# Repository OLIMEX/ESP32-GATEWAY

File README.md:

# ESP32-GATEWAY
ESP32 WiFi / BLE development board with Ethernet, microSD card, GPIOs, made with KiCAD

Board page: https://www.olimex.com/Products/IoT/ESP32/ESP32-GATEWAY/open-source-hardware

Hardware is released under Apache 2.0 License

Box design is released under CC BY 4.0 License

Software is released under GPL3 License

Documentation is released under CC BY-SA 3.0

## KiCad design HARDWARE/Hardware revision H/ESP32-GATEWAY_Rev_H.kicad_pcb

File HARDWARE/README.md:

# ESP32-GATEWAY
ESP32 WIFI / BLE development board with Ethernet, micro SD card, GPIOs made with KiCAD.

Notice that we use the latest nightly KiCad builds.

Hardware change log:

- Hardware revision I

1. To reduce noise getting picked by Ethernet clock, disconnected GPIO17 from the CON1 header. Added 
jumper pads GPIO17_E1 (open by default) if somebody wants to lead it to the header...

---

- Hardawre revision H

1. Added diode D5 on esp_en;
3. Added TVS1 on PHY;
4. Opravi se value na NA(HN1x20);
5. T1 now LMUN2211LT1G;
6. USB connector changed to type C (more popular nowadays);
7. Added r12 and c6;
8. Added CE sign;
9. R28,R31,R32,R33 lowered to 0402 size;
10. DCDC - SY8089 changed to TPS62A02ADRLR. C3 now NA. L2 changed to 1.0uH/2.5A/CD32;
11. Updated the CH340X module to the latest one. 

---

- Hardware revision G

1. R54 removed. R24 and R16 moved further away from the button.
2. Improved EN signal - added C5(1uF/0603) on pin #3 of ESP32. R24 now 10k.

---

- Hardware revision F

- Added 3D view. Major changes to GPIO header, SD card mode, power consumption!:

1. GPIO6-11, which are used by the ESP32's internal flash, were disconnected from CON1 
and the 6 SD card signals are now routed instead for use when SD card is not present;
2.  SD card changed from 4-bit mode of operation to 1-bit mode of operation! Added 3 
NA resistor pads (R9-R11) for backwards compatiblity.
3. A lot of deep sleep mode improvements to lower the consumption to 100uA or less:

- R19 was changed from 4.99k/1%/R0603 to 220k/R0603;

- R20 was changed from 1.1k/1%/R0603 to 49.9k/1%/R0603;

- R30 was changed from 10k/0603 to 1M/R0603;

- LED_E1 jumper added to provide an option to disable the power LED;

- R24 changed from 1k/0603 to 1M/R0603;

- U5(CH340)'s pin 20disconnected from GND and left opened;

- CH340 now powered only when USB is present;

- R35 and R40 were changed from 220R/R0603 to 10k/R0603;

- D1 and D3 added, 1N5819S4/SOD123, as level shifters;

4. L2 was changed from 2.2uH/1.5A/DCR<0.1R/CD32 to 2.2uH/1.5A/DCR=72mR/20%/3.00x3.00x1.50mm/CD32(NR3015T2R2M);
5. U3's value was changed from ESP-WROOM-32 to ESP32-WROOM-32D-4MB;
6. U9(BAT54C(SOT23-3)) was renamed to D4;

---

- Hardware revision E1

1. Added C2/22uF/0603 for slower PHY powering

- Hardware revision E

1. R5 connected after T1's collector and value changed from NA to 1K. 
2. Improved drill distances.

- Hardware revision D

>Major Ethernet schematic changes, now similar to ESP32-PoE:

1. LAN8710's pin XTAL1 was disconnected from GPIO0 and connected to GPIO17/EMAC_CLK_OUT_180. GPIO17 
is now source clock. GPIO5 is now used as Ethernet "power enable pin".
2. CR1(Q50MHz/25ppm/3V/4P/5x3.2mm) and all surrounding elements were deleted.
3. U8(NCP303LSN27T1G(SOT-23-5)) and all surrounding elements were deleted.
4. U10(BAT54C), R44 and R5 were deleted.
5. FET1, R5, R6, C2, T1 and L1 were added to enable Ethernet power on/off feature.
6. GPIO5 is used for Ethernet power on/off.

- Hardware revision C

1. R5(1k) resistor added between OSC_EN and NRST(pin #19) of LAN8710A chip. Later, it was changed to NA!
2. U2 changed from SY8009AAAC(SOT23-5) to SY8089AAAC(SOT23-5).
3. FET2 changed from IRLML6402 to WPM2015-3/TR.
4. ESP32-WROOM module pad improvements 

>Major changes to the Ethernet PHY and reset similar to EVB's_Rev_D1:

5. U8 changed from BD5230G-TR(SSOP5/SOT-23-5) to NCP303LSN27T1G(SOT-23-5).
6. C28 changed from 10nF/50V/20%/Y5V/C0603 to 470nF/16V/10%/X7R/C0603.
7. C18 changed from 10uF/6.3V/20%/X5R/C0603 to NA.
8. R38 changed from 100k to 10k/R0603.
9. R5 changed from 1k/R0603 to NA.

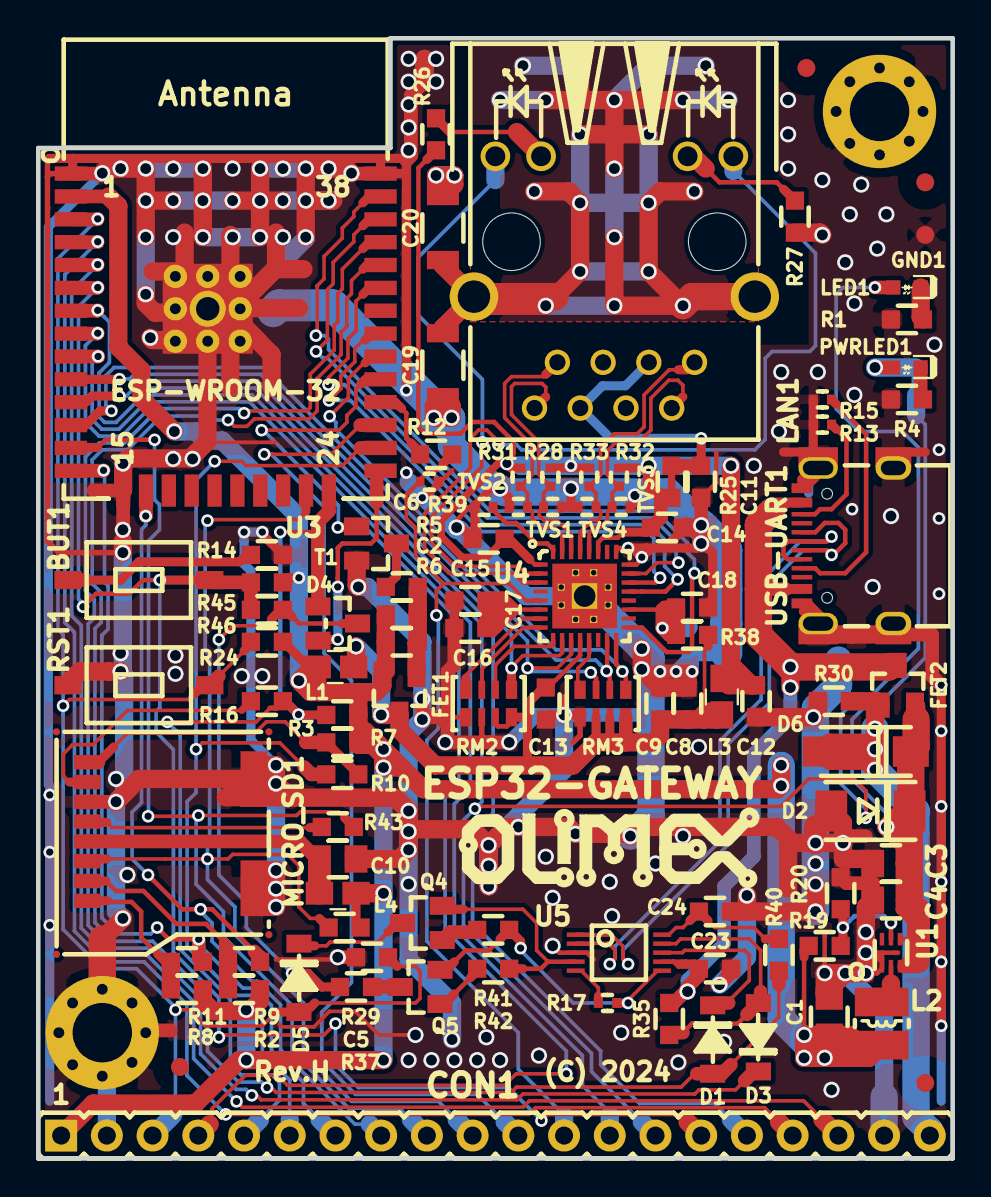
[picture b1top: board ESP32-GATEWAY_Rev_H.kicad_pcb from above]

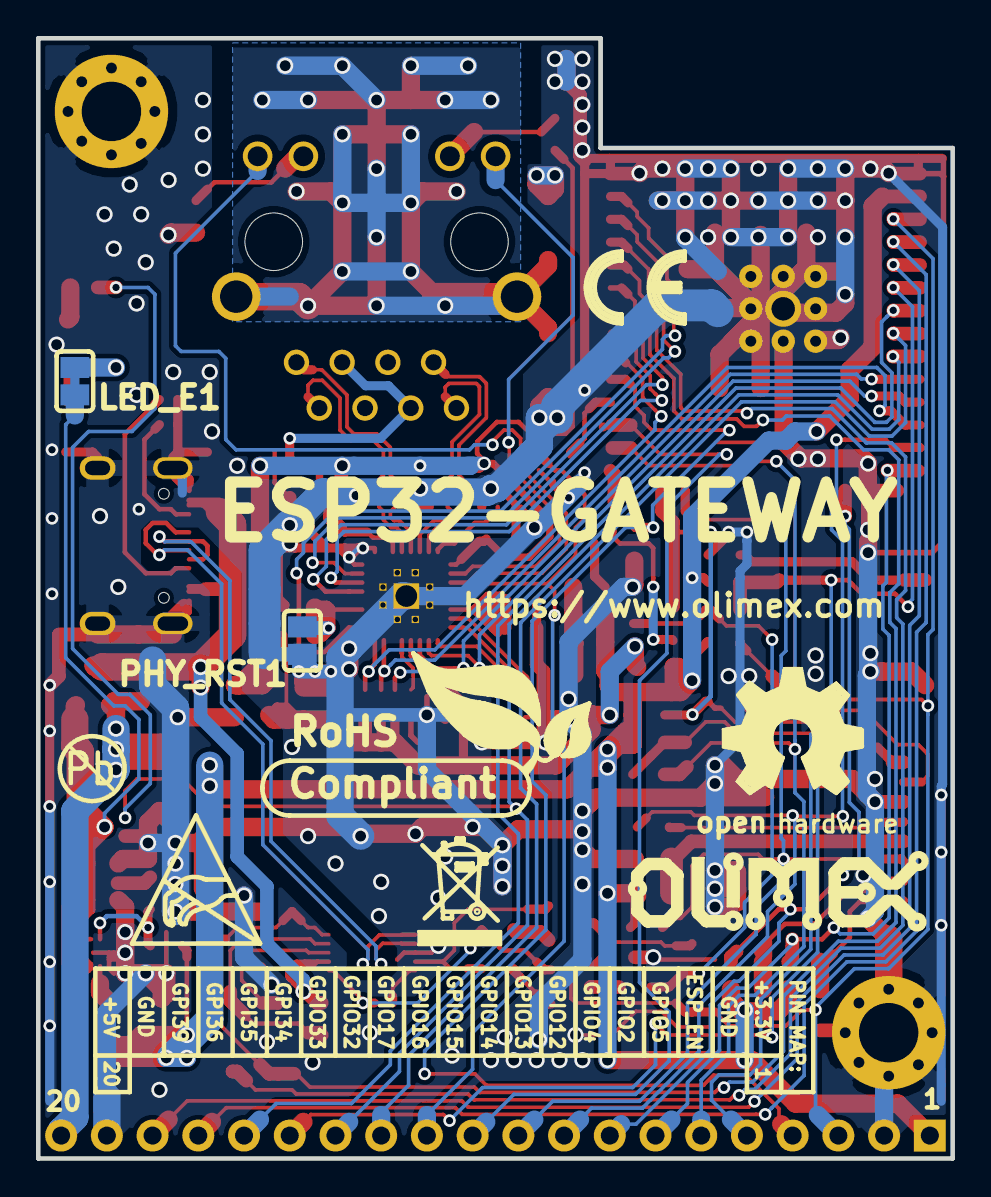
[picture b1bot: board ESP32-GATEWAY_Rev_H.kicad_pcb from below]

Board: 2 copper layers, 50.8 x 62.2 mm, 110 parts (9 on the bottom side), 79 nets.

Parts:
BUT1: T1107A(6x3,8x2,5MM)
C1, C4, C10: 47uF/6.3V/20%/X5R/C0805; C_0805_5MIL_DWS
C2, C8, C9, C12, C23: 22uF/6.3V/20%/X5R/C0603; C_0603_5MIL_DWS
C3: NA(47uF/6.3V/20%/X5R/C0805); C_0805_5MIL_DWS
C5: 1uF/C0603; C_0603_5MIL_DWS
C6: NA/C0402; C_0402_5MIL_DWS
C11, C13, C14, C15, C17, C24: 100nF/50V/20%/Y5V/C0603; C_0603_5MIL_DWS
C16: 2.2uF/6.3V/10%/X5R/C0603; C_0603_5MIL_DWS
C18: NA(10uF/6.3V/20%/X5R/C0603); C_0603_5MIL_DWS
C19: 1nF/2000V/10%/X7R/C1206; C_1206_5MIL_DWS_ISO
C20: NA(1nF/2000V/10%/X7R/C1206); C_1206_5MIL_DWS_ISO
CON1: NA(HN1x20); HN1x20
D1, D3, D5: 1N5819S4/SOD123; SOD-123_1C-2A_KA
D2: SMBJ6.0A(DO-214AA); DO214AA_1(K)-2(A)
D4: BAT54C(SOT23-3); SOT23-3
D6: 1N5822/SS34/SMA; SMA-KA
FET1, FET2: WPM2015-3/TR; SOT23
FID1, FID3: Fiducial; Fiducial1x3
FID2, FID4: Fiducial; Fiducial1x3_Past
GND1: TESTPAD; TESTPAD_40-ROUND
L1: NA(FB0805/600R/2A); L_0805_5MIL_DWS
L2: 1.0uH/2.5A/DCR=30mR/20%/3.00x3.00x1.50mm/CD32(SWP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; CD32
L3, L4: 600OHM/2A/UPZ2012E-601-2R0TF; L_0805_5MIL_DWS
LAN1: RJLD-060TC1(LPJ4013EDNL); RJLBC-060TC1
LED1: LED/GREEN/0603; LED_0603_KA
LED_E1: Closed; SJ
Logo-OLimeX: OLIMEX_LOGO_TB
Logo-OSHW: LOGO_OPENHARDWARE_8x8
Logo-OlimexBIG: OLIMEX_LOGO_TB
MH1, MH2: Mounting_hole_Shield_3.3mm
MICRO_SD1: TFC-WXCP11-08-LF
PHY_RST1: Opened; SJ
PWRLED1: LED/RED/0603; LED_0603_KA
Q4, Q5: BC817-40(SOT23); SOT23
R1, R2, R3, R4, R7, R8: 2.2k/R0603; R_0603_5MIL_DWS
R5, R41, R42: 1k/R0603; R_0603_5MIL_DWS
R6, R24, R29, R35, R38, R40, R45: 10k/R0603; R_0603_5MIL_DWS
R9, R10, R11, R46: NA/R0603; R_0603_5MIL_DWS
R12: 33R/R0603; R_0603_5MIL_DWS
R13, R15: 5.1k/1%/R0402; R_0402_5MIL_DWS
R14, R16, R37: 220R/R0603; R_0603_5MIL_DWS
R17: 4.7k/R0402; R_0402_5MIL_DWS
R19: 220k/R0603; R_0603_5MIL_DWS
R20: 49.9k/1%/R0603; R_0603_5MIL_DWS
R25: 0R(Board_Mounted); R_0603_5MIL_DWS
R26, R27: 330R/R0603; R_0603_5MIL_DWS
R28, R31, R32, R33: 49.9R/1%/R0402; R_0402_5MIL_DWS
R30: 1M/R0603; R_0603_5MIL_DWS
R39: 12.1k/1%/R0402; R_0402_5MIL_DWS
R43: 10R/R0603; R_0603_5MIL_DWS
RM2, RM3: RA1206_(4X0603)_4B8_2.2k; R_MATRIX_4
RST1: T1107A(6x3,8x2,5MM)
Sign-Antistatic: Val**; LOGO_ANTISTATIC_1
Sign-RecyclBin: LOGO_RECYCLEBIN_1
Sign_CE: CE_Sign
Sign_Pb-Free: LOGO_PBFREE
Sign_RoHS: Val**; LOGO_ROHS_1
T1: LMUN2211LT1G; SOT23
TVS1, TVS2, TVS3, TVS4: GG0402052R542P; D_0402_5MIL_DWS
U1: TPS62A02ADRLR(SOT-563-6); SOT-563-6
U3: ESP32-WROOM-32E-N4; ESP-WROOM-32_MODULE
U4: LAN8710A-EZC-ABC; QFN32_EP(33)_5.00x5.00x0.90mm_Pitch_0.50mm
U5: CH340X(MSOP-10); MSOP-10_Pitch-0.5mm_3.00x3.00x1.00mm
USB-UART1: USB-C-16P-F-PTH; USB2.0_TYPE-C(A40-00119-A52-12)

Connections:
+3.3VLAN: C8.1, C9.1, C13.1, FET1.3, L1.2, L3.1, R38.2, RM2.3.1, RM2.4.1, RM3.1.2, RM3.2.2, RM3.3.2, U4.12
+3V3: C1.1, C2.1, CON1.1, FET1.2, L1.1, L2.2, L4.1, R2.1, R3.1, R6.1, R7.1, R8.1, R19.2, R24.1, R29.1, R45.1, U3.2
+5V: C3.1, C4.1, D2.1, D6.1, FET2.2, LED_E1.1, LED_E1.2, PWRLED1.2, U1.3, U1.4
+5V_EXT: CON1.20, D6.2, FET2.1, R30.1
/+5V_USB: C23.1, FET2.3, R35.1, U5.7, USB-UART1.A4, USB-UART1.A9, USB-UART1.B4, USB-UART1.B9
/D+: U5.1, USB-UART1.A6, USB-UART1.B6
/D-: U5.2, USB-UART1.A7, USB-UART1.B7
/D_Com: D4.3, R37.2, R46.2
/ESP_EN: C5.1, CON1.3, D5.2, R24.2, RST1.1, U3.3
/GPI34\BUT1: BUT1.1, CON1.15, R45.2, R46.1, U3.6
/GPI35: CON1.16, U3.7
/GPI36: CON1.17, U3.4
/GPI39: CON1.18, U3.5
/GPIO0: D4.2, U3.25
/GPIO1\U0TXD: D3.1, U3.35
/GPIO2\HS2_DATA0: CON1.5, D4.1, R3.2, R16.1, U3.24
/GPIO3\U0RXD: D1.2, R40.2, U3.34
/GPIO4\HS2_DATA1: CON1.6, R10.1, U3.26
/GPIO5\PHY_PWR: CON1.4, T1.1, U3.29
/GPIO12\HS2_DATA2: CON1.7, R11.1, U3.14
/GPIO13\HS2_DATA3: CON1.8, R9.1, U3.16
/GPIO14\HS2_CLK: CON1.9, R43.1, U3.13
/GPIO15\HS2_CMD: CON1.10, MICRO_SD1.3, R29.2, U3.23
/GPIO16: CON1.11, U3.27
/GPIO17\EMAC_CLK_OUT_180: C6.1, CON1.12, R12.2, U4.5
/GPIO18\MDIO(RMII): RM3.1.1, U3.30, U4.16
/GPIO19\EMAC_TXD0(RMII): U3.31, U4.22
/GPIO21\EMAC_TX_EN(RMII): U3.33, U4.21
/GPIO22\EMAC_TXD1(RMII): U3.36, U4.23
/GPIO23\MDC(RMII): U3.37, U4.17
/GPIO25\EMAC_RXD0(RMII): RM3.3.1, U3.10, U4.11
/GPIO26\EMAC_RXD1(RMII): RM2.4.2, U3.11, U4.10
/GPIO27\EMAC_RX_CRS_DV: RM3.2.1, U3.12, U4.15
/GPIO32: CON1.13, U3.8
/GPIO33\LED: CON1.14, LED1.2, U3.9
/PHYAD0: RM3.4.1, U4.13
/PHYAD1: RM2.1.2, U4.7
/PHYAD2: RM2.2.2, U4.8
/RMIISEL: RM2.3.2, U4.9
/VDD1A-2A: C11.1, C12.1, C14.1, C15.1, L3.2, LAN1.3, LAN1.6, R25.1, R25.2, R26.1, R28.1, R31.1, R32.1, R33.1, U4.1, U4.27
/VDDCR: C16.1, C17.1, U4.6
GND: C1.2, C3.2, C4.2, C5.2, C6.2, C8.2, C9.2, C10.2, C11.2, C12.2, C13.2, C14.2, C15.2, C16.2, C17.2, C18.1, C19.2, C20.2, C23.2, C24.2, CON1.2, CON1.19, D2.2, GND1.1, MH1.GND1, MH2.GND1, MICRO_SD1.6, MICRO_SD1.SH1, MICRO_SD1.SH2, PHY_RST1.1, R1.1, R4.2, R13.2, R14.2, R15.2, R20.2, R27.2, R30.2, R39.2, RM2.1.1, RM2.2.1, RM3.4.2, RST1.2, T1.2, TVS1.1, TVS2.1, TVS3.2, TVS4.2, U1.1, U3.1, U3.15, U3.38, U3.39, U4.24, U4.25, U4.33, U5.3, USB-UART1.0, USB-UART1.A1, USB-UART1.A12, USB-UART1.B1, USB-UART1.B12
unnamed: BUT1.2, R14.1
unnamed: C2.2, FET1.1, R5.1, R6.2
unnamed: C10.1, L4.2, MICRO_SD1.4
unnamed: C18.2, PHY_RST1.2, R38.1, U4.19
unnamed: C19.1, C20.1, LAN1.GND1, LAN1.GND2
unnamed: C24.1, R40.1, U5.10
unnamed: D1.1, U5.8
unnamed: D3.2, R35.2, U5.9
unnamed: D5.1, Q4.3
unnamed: L2.1, U1.2
unnamed: LAN1.1, R33.2, TVS4.1, U4.29
unnamed: LAN1.2, R32.2, TVS3.1, U4.28
unnamed: LAN1.7, R31.2, TVS2.2, U4.31
unnamed: LAN1.8, R28.2, TVS1.2, U4.30
unnamed: LAN1.AG1, R26.2
unnamed: LAN1.AY1, U4.3
unnamed: LAN1.KG1, U4.2
unnamed: LAN1.KY1, R27.1
unnamed: LED1.1, R1.2
unnamed: MICRO_SD1.1, R8.2, R11.2
unnamed: MICRO_SD1.2, R2.2, R9.2
unnamed: MICRO_SD1.5, R43.2
unnamed: MICRO_SD1.7, R16.2
unnamed: MICRO_SD1.8, R7.2, R10.2
unnamed: PWRLED1.1, R4.1
unnamed: Q4.1, R41.2
unnamed: Q4.2, R42.1, U5.4
unnamed: Q5.1, R42.2
unnamed: Q5.2, R17.2, R41.1, U5.6
unnamed: Q5.3, R37.1
unnamed: R5.2, T1.3
unnamed: R12.1, U3.28
unnamed: R13.1, USB-UART1.B5
unnamed: R15.1, USB-UART1.A5
unnamed: R17.1, U5.5
unnamed: R19.1, R20.1, U1.5
unnamed: R39.1, U4.32

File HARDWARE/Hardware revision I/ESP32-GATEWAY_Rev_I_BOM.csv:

"Id";"Designator";"Package";"Quantity";"Designation";"Supplier and ref";
1;"U4";"QFN32_EP(33)_5.00x5.00x0.90mm_Pitch_0.50mm";1;"LAN8710A-EZC-ABC";;;
2;"USB-UART1";"USB2.0_TYPE-C(A40-00119-A52-12)";1;"USB-C-16P-F-PTH";;;
3;"D3,D1,D5";"SOD-123_1C-2A_KA";3;"1N5819S4/SOD123";;;
4;"R19";"R_0603_5MIL_DWS";1;"220k/R0603";;;
5;"R35,R29,R6,R45,R40,R38,R24";"R_0603_5MIL_DWS";7;"10k/R0603";;;
6;"U5";"MSOP-10_Pitch-0.5mm_3.00x3.00x1.00mm";1;"CH340X(MSOP-10)";;;
7;"U3";"ESP-WROOM-32_MODULE";1;"ESP32-WROOM-32E-N4";;;
8;"Sign_CE";"CE_Sign";1;"CE_Sign";;;
9;"LED_E1";"SJ";1;"Closed";;;
10;"MICRO_SD1";"TFC-WXCP11-08-LF";1;"TFC-WXCP11-08-LF";;;
11;"Logo-OlimexBIG,Logo-OLimeX";"OLIMEX_LOGO_TB";2;"";;;
12;"R5,R42,R41";"R_0603_5MIL_DWS";3;"1k/R0603";;;
13;"L1";"L_0805_5MIL_DWS";1;"NA(FB0805/600R/2A)";;;
14;"C2,C23,C12,C9,C8";"C_0603_5MIL_DWS";5;"22uF/6.3V/20%/X5R/C0603";;;
15;"T1";"SOT23";1;"LMUN2211LT1G";;;
16;"FET1,FET2";"SOT23";2;"WPM2015-3/TR";;;
17;"D2";"DO214AA_1(K)-2(A)";1;"SMBJ6.0A(DO-214AA)";;;
18;"R3,R2,R1,R4,R8,R7";"R_0603_5MIL_DWS";6;"2.2k/R0603";;;
19;"Sign_RoHS";"LOGO_ROHS_1";1;"Val**";;;
20;"Sign-RecyclBin";"LOGO_RECYCLEBIN_1";1;"";;;
21;"Sign_Pb-Free";"LOGO_PBFREE";1;"";;;
22;"Logo-OSHW";"LOGO_OPENHARDWARE_8x8";1;"";;;
23;"Sign-Antistatic";"LOGO_ANTISTATIC_1";1;"Val**";;;
24;"LED1";"LED_0603_KA";1;"LED/GREEN/0603";;;
25;"CON1";"HN1x20";1;"NA(HN1x20)";;;
26;"R37,R16,R14";"R_0603_5MIL_DWS";3;"220R/R0603";;;
27;"C4,C10,C1";"C_0805_5MIL_DWS";3;"47uF/6.3V/20%/X5R/C0805";;;
28;"C3";"C_0805_5MIL_DWS";1;"NA(47uF/6.3V/20%/X5R/C0805)";;;
29;"R20";"R_0603_5MIL_DWS";1;"49.9k/1%/R0603";;;
30;"R46,R10,R9,R11";"R_0603_5MIL_DWS";4;"NA/R0603";;;
31;"R30";"R_0603_5MIL_DWS";1;"1M/R0603";;;
32;"D6";"SMA-KA";1;"1N5822/SS34/SMA";;;
33;"C24,C17,C15,C14,C13,C11";"C_0603_5MIL_DWS";6;"100nF/50V/20%/Y5V/C0603";;;
34;"C20";"C_1206_5MIL_DWS_ISO";1;"NA(1nF/2000V/10%/X7R/C1206)";;;
35;"C19";"C_1206_5MIL_DWS_ISO";1;"1nF/2000V/10%/X7R/C1206";;;
36;"R43";"R_0603_5MIL_DWS";1;"10R/R0603";;;
37;"R27,R26";"R_0603_5MIL_DWS";2;"330R/R0603";;;
38;"PWRLED1";"LED_0603_KA";1;"LED/RED/0603";;;
39;"GND1";"TESTPAD_40-ROUND";1;"TESTPAD";;;
40;"C18";"C_0603_5MIL_DWS";1;"NA(10uF/6.3V/20%/X5R/C0603)";;;
41;"C16";"C_0603_5MIL_DWS";1;"2.2uF/6.3V/10%/X5R/C0603";;;
42;"PHY_RST1,GPIO17_E1";"SJ";2;"Opened";;;
43;"MH1,MH2";"Mounting_hole_Shield_3.3mm";2;"Mounting_hole_Shield_3.3mm";;;
44;"L4,L3";"L_0805_5MIL_DWS";2;"600OHM/2A/UPZ2012E-601-2R0TF";;;
45;"Q5,Q4";"SOT23";2;"BC817-40(SOT23)";;;
46;"L2";"CD32";1;"1.0uH/2.5A/DCR=30mR/20%/3.00x3.00x1.50mm/CD32(SWPA3015S1R0MT)";;;
47;"RM3,RM2";"R_MATRIX_4";2;"RA1206_(4X0603)_4B8_2.2k";;;
48;"RST1,BUT1";"T1107A(6x3,8x2,5MM)";2;"T1107A(6x3,8x2,5MM)";;;
49;"D4";"SOT23-3";1;"BAT54C(SOT23-3)";;;
50;"FID1,FID3";"Fiducial1x3";2;"Fiducial";;;
51;"R25";"R_0603_5MIL_DWS";1;"0R(Board_Mounted)";;;
52;"C5";"C_0603_5MIL_DWS";1;"1uF/C0603";;;
53;"LAN1";"RJLBC-060TC1";1;"RJLD-060TC1(LPJ4013EDNL)";;;
54;"R12";"R_0603_5MIL_DWS";1;"33R/R0603";;;
55;"R28,R31,R32,R33";"R_0402_5MIL_DWS";4;"49.9R/1%/R0402";;;
56;"FID4,FID2";"Fiducial1x3_Past";2;"Fiducial";;;
57;"TVS2,TVS3,TVS4,TVS1";"D_0402_5MIL_DWS";4;"GG0402052R542P";;;
58;"C6";"C_0402_5MIL_DWS";1;"NA/C0402";;;
59;"R39";"R_0402_5MIL_DWS";1;"12.1k/1%/R0402";;;
60;"U1";"SOT-563-6";1;"TPS62A02ADRLR(SOT-563-6)";;;
61;"R13,R15";"R_0402_5MIL_DWS";2;"5.1k/1%/R0402";;;
62;"R17";"R_0402_5MIL_DWS";1;"4.7k/R0402";;;

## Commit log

2017-06-21 initial update ESP32-GATEWAY KiCAD files
2017-09-12 Updated hardware revision B
2018-03-27 Tested demos update
    ESP-IDF demos tested with ESP32-GATEWAY
2018-03-27 update
    Links to pictures updated
2018-03-27 update
    links
2018-07-31 update
    hardware revision C
2019-01-04 Update
    Revison D and E and revision changes.
2019-04-05 Update
    new demo for boards from hardware revision D or newer
2019-09-23 Fix
    Wrong sources were uploaded by mistake
2019-12-09 Update
    Added sources and notes revision F
2020-05-12 Update
    Added revision G
2020-05-12 Update
    changelog
2020-07-16 Added example
    Added ethernet example for ESP-IDF 4.0 and 4.0.1
2020-10-22 Update
    "Toggle_relay" project renamed to "led_button" to avoid confusion since there is not relay but only LED on Gateway board.
2022-08-31 Galeri
    Photo video
2024-10-08 Update
    Revisions H and I
2024-10-10 Update
    New hardware revision changes the USB connector
2025-07-18 Update sdkconfig
    Changed Eth reset pin value from -1 to 5
2026-01-19 Update
    Added plastic box design

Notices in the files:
HARDWARE/Hardware revision H/ESP32-GATEWAY_Rev_H.kicad_pcb:
(C) 2024
